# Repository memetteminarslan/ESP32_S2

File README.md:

# ESP32C3_Kicanvas
readme memin

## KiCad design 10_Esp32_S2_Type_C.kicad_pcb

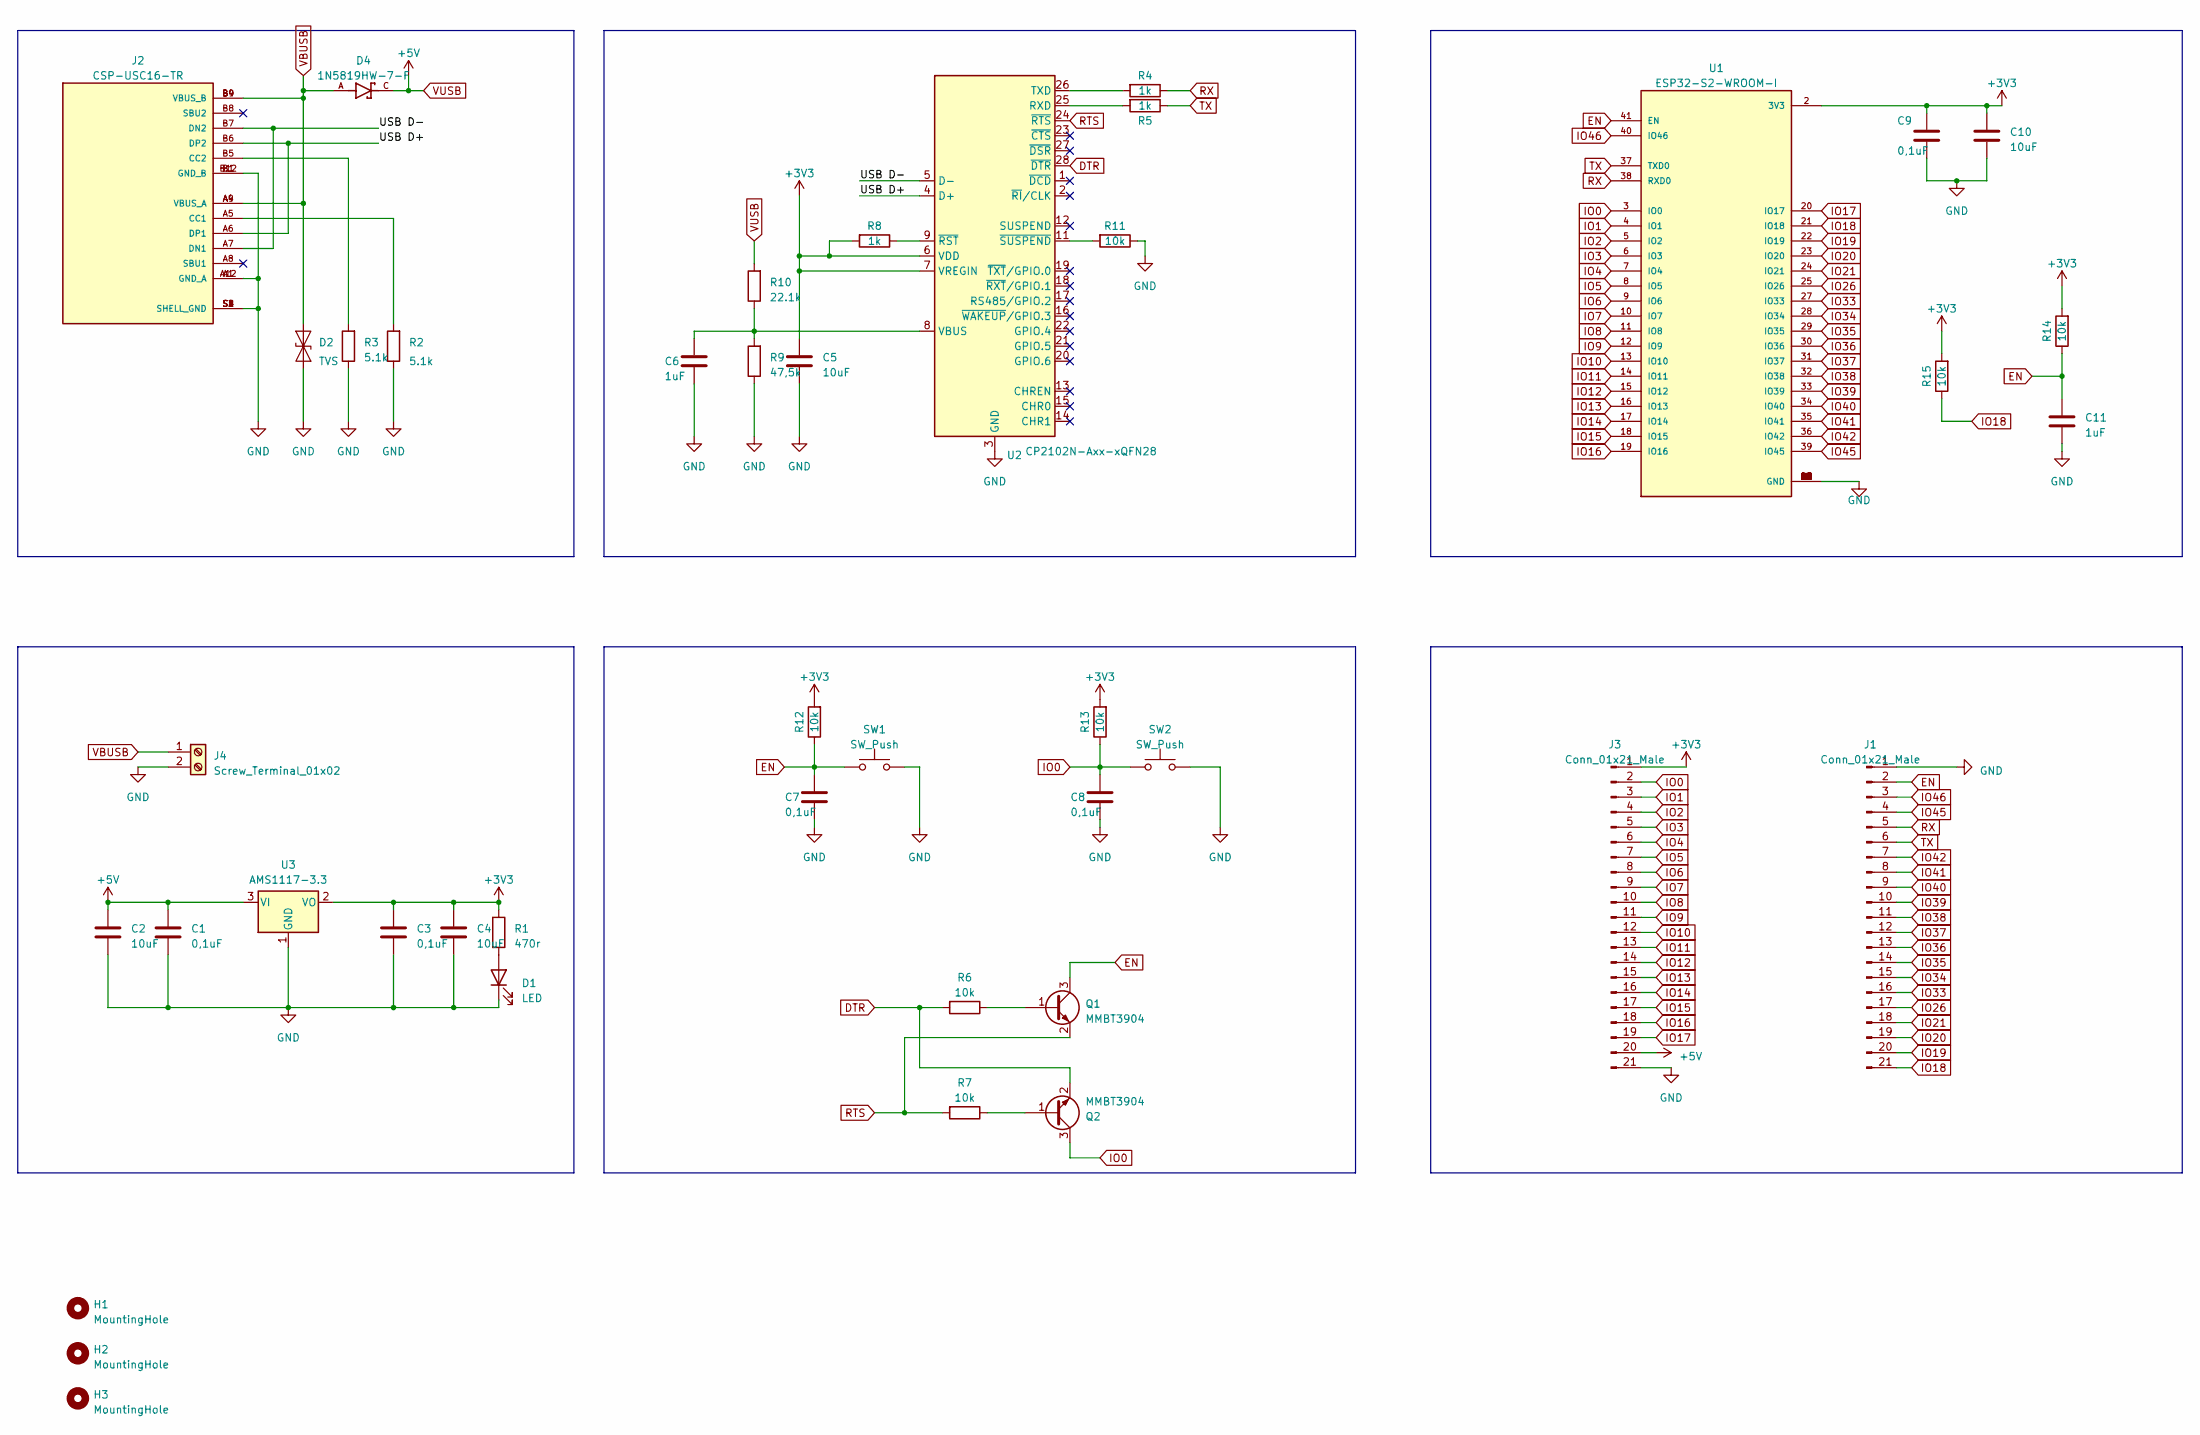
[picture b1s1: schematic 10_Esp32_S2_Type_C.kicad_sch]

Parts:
C1, C3, C7, C8, C9: 0,1uF; C_0603_1608Metric
C2, C4, C5, C10: 10uF; C_0603_1608Metric
C6, C11: 1uF; C_0603_1608Metric
D1: LED; LED_0603_1608Metric
D2: TVS; D_SOD-323
D4: 1N5819HW-7-F; SOD3715X145N; PARTREV 18-2
H1, H2, H3: MountingHole; MountingHole_2.5mm
J1, J3: Conn_01x21_Male; PinHeader_1x21_P2.54mm_Vertical
J2: CSP-USC16-TR; VALCON_CSP-USC16-TR; PARTREV A0
J4: Screw_Terminal_01x02; PinHeader_1x02_P2.54mm_Vertical
Q1, Q2: MMBT3904; SOT-23
R1: 470r; R_0603_1608Metric
R2, R3: 5.1k; R_0402_1005Metric
R4, R5, R8: 1k; R_0603_1608Metric
R6, R7, R11, R12, R13, R14, R15: 10k; R_0603_1608Metric
R9: 47,5k; R_0603_1608Metric
R10: 22.1k; R_0603_1608Metric
SW1, SW2: SW_Push; SW_TL1015AF160QG
U1: ESP32-S2-WROOM-I; ESP32-S2-WROOM; PARTREV v1.3
U2: CP2102N-Axx-xQFN28; QFN-28-1EP_5x5mm_P0.5mm_EP3.35x3.35mm
U3: AMS1117-3.3; SOT-223-3_TabPin2

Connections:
+3V3: C3.1, C4.1, C5.1, C9.1, C10.1, J3.1, R1.1, R8.2, R12.2, R13.2, R14.2, R15.2, U1.2 (3V3), U2.6 (VDD), U2.7 (VREGIN), U3.2 (VO)
/USB D+: J2.A6 (DP1), J2.B6 (DP2), U2.4 (D+)
/USB D-: J2.A7 (DN1), J2.B7 (DN2), U2.5 (D-)
DTR: Q2.2 (E), R6.2, U2.28 (~DTR)
EN: C7.1, C11.1, J1.2, Q1.3 (C), R12.1, R14.1, SW1.1, U1.41 (EN); also elsewhere on the board
GND: C1.2, C2.2, C3.2, C4.2, C5.2, C6.2, C7.2, C8.2, C9.2, C10.2, C11.2, D1.1 (K), D2.1 (A1), J1.1, J2.A1 (GND_A), J2.A12 (GND_A), J2.B1 (GND_B), J2.B12 (GND_B), J2.S1 (SHELL_GND), J2.S2 (SHELL_GND), J2.S3 (SHELL_GND), J2.S4 (SHELL_GND), J3.21, J4.2, R2.1, R3.1, R9.1, R11.1, SW1.2, SW2.2, U1.1 (GND), U1.26 (GND), U1.42 (GND), U1.43 (GND), U1.44 (GND), U1.45 (GND), U1.46 (GND), U1.47 (GND), U1.48 (GND), U1.49 (GND), U1.50 (GND), U1.51 (GND), U2.3 (GND), U2.29 (GND), U3.1 (GND); also elsewhere on the board
IO0: C8.1, J3.2, Q2.3 (C), R13.1, SW2.1, U1.3 (IO0); also elsewhere on the board
IO1: J3.3, U1.4 (IO1)
IO2: J3.4, U1.5 (IO2)
IO3: J3.5, U1.6 (IO3)
IO4: J3.6, U1.7 (IO4)
IO5: J3.7, U1.8 (IO5)
IO6: J3.8, U1.9 (IO6)
IO7: J3.9, U1.10 (IO7)
IO8: J3.10, U1.11 (IO8)
IO9: J3.11, U1.12 (IO9)
IO10: J3.12, U1.13 (IO10)
IO11: J3.13, U1.14 (IO11)
IO12: J3.14, U1.15 (IO12)
IO13: J3.15, U1.16 (IO13)
IO14: J3.16, U1.17 (IO14)
IO15: J3.17, U1.18 (IO15)
IO16: J3.18, U1.19 (IO16)
IO17: J3.19, U1.20 (IO17)
IO18: J1.21, R15.1, U1.21 (IO18)
IO19: J1.20, U1.22 (IO19)
IO20: J1.19, U1.23 (IO20)
IO21: J1.18, U1.24 (IO21)
IO26: J1.17, U1.25 (IO26)
IO33: J1.16, U1.27 (IO33)
IO34: J1.15, U1.28 (IO34)
IO35: J1.14, U1.29 (IO35)
IO36: J1.13, U1.30 (IO36)
IO37: J1.12, U1.31 (IO37)
IO38: J1.11, U1.32 (IO38)
IO39: J1.10, U1.33 (IO39)
IO40: J1.9, U1.34 (IO40)
IO41: J1.8, U1.35 (IO41)
IO42: J1.7, U1.36 (IO42)
IO45: J1.4, U1.39 (IO45)
IO46: J1.3, U1.40 (IO46)
unnamed: D1.2 (A), R1.2
unnamed: J2.A5 (CC1), R2.2
unnamed: J2.B5 (CC2), R3.2
unnamed: Q1.1 (B), R6.1
unnamed: Q2.1 (B), R7.1
unnamed: R5.2, U2.25 (RXD)
unnamed: R4.2, U2.26 (TXD)
unnamed: C6.1, R9.2, R10.1, U2.8 (VBUS)
unnamed: R8.1, U2.9 (~RST)
unnamed: R11.2, U2.11 (~SUSPEND)
RTS: Q1.2 (E), R7.2, U2.24 (~RTS)
RX: J1.5, R4.1, U1.38 (RXD0)
TX: J1.6, R5.1, U1.37 (TXD0)
VBUSB: D2.2 (A2), D4.A, J2.A4 (VBUS_A), J2.A9 (VBUS_A), J2.B4 (VBUS_B), J2.B9 (VBUS_B), J4.1
VUSB: C1.1, C2.1, D4.C, J3.20, R10.2, U3.3 (VI)

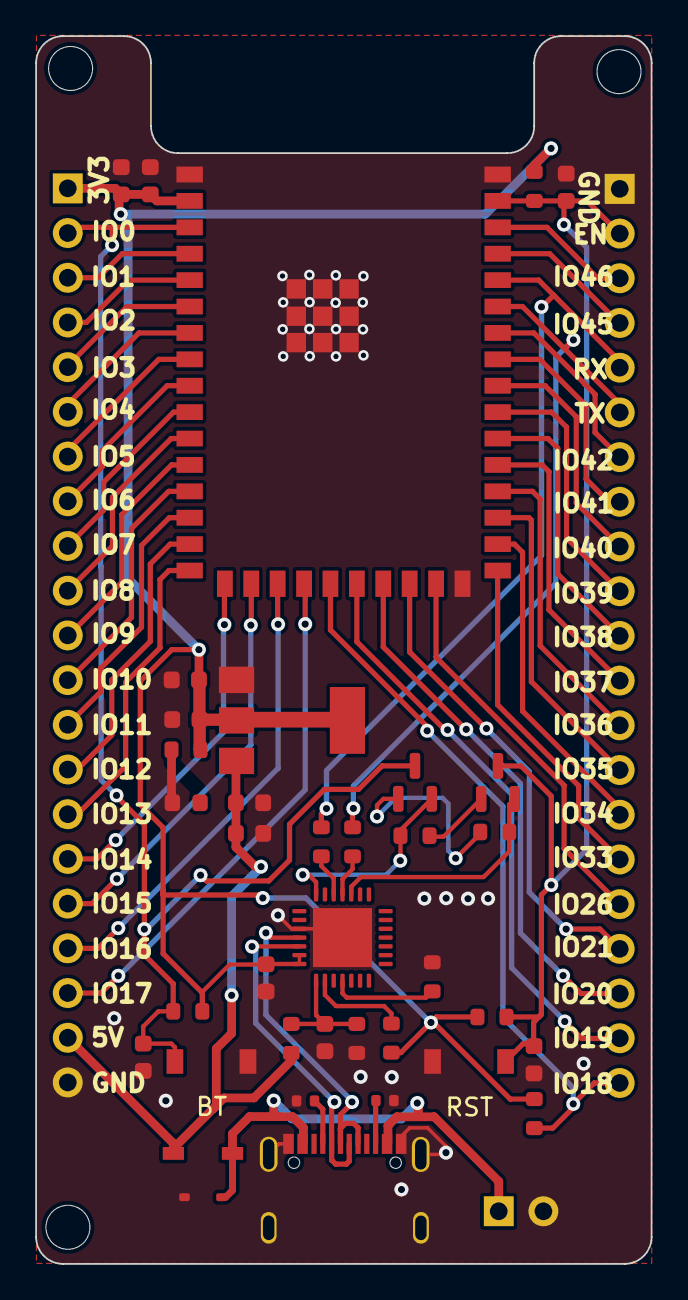
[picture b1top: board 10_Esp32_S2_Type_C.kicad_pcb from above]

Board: 2 copper layers, 35.0 x 69.8 mm, 43 parts (0 on the bottom side), 56 nets.

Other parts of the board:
BT: SW_Push; SW_TL1015AF160QG
RST: SW_Push; SW_TL1015AF160QG

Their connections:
EN: RST.1; also elsewhere on the board
GND: BT.2, RST.2; also elsewhere on the board
IO0: BT.1; also elsewhere on the board

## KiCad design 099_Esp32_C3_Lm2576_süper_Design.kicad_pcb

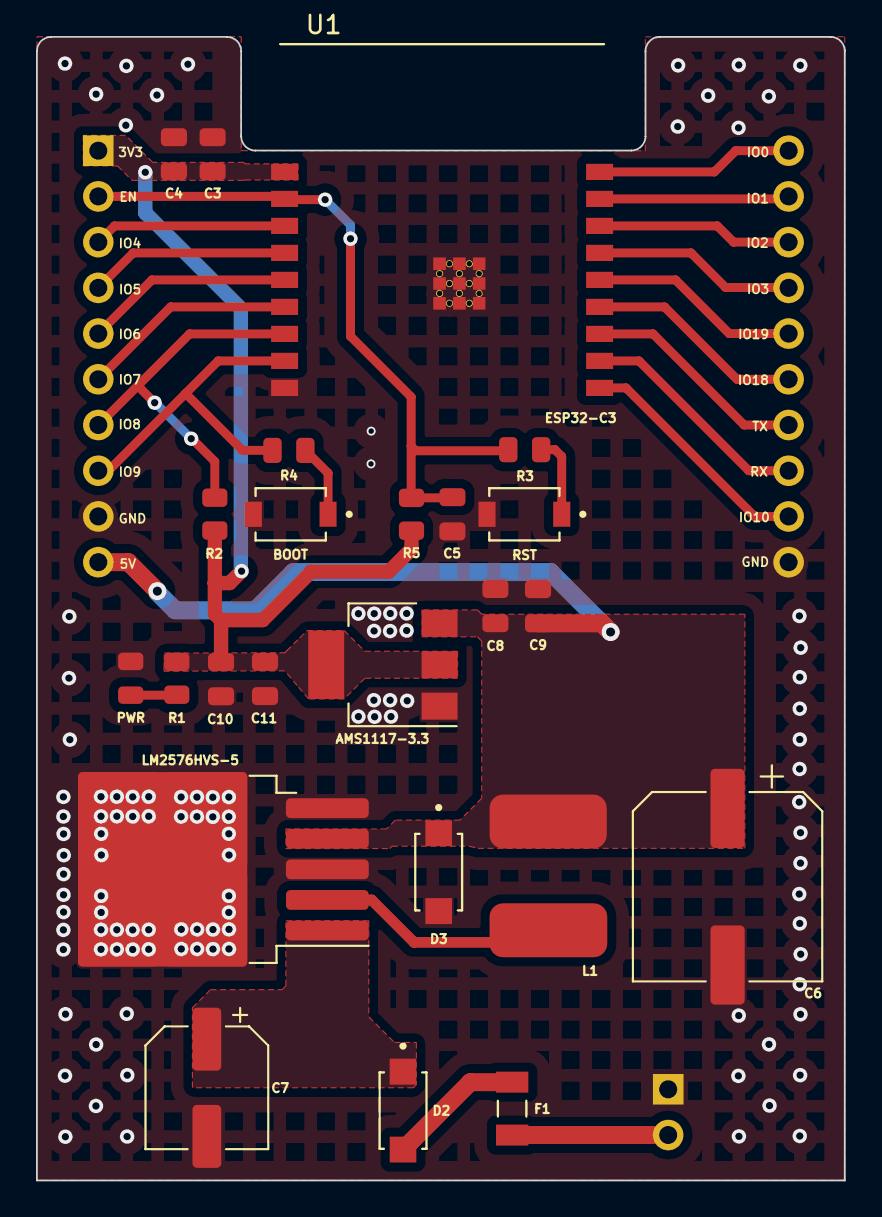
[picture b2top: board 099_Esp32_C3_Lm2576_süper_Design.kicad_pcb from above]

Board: 2 copper layers, 44.9 x 63.5 mm, 27 parts (0 on the bottom side), 26 nets.

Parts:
BOOT: SW_Push; SW_TL1015AF160QG
C3, C4, C5, C8, C9, C10, C11: C; C_0805_2012Metric
C6: C_Polarized_Small; CP_Elec_10x12.6
C7: C_Polarized_Small; CP_Elec_6.3x7.7
D2, D3: SS310ALH; SODFL5226X100N
F1: Fuse; FUSC3215X83N
J3: Screw_Terminal_01x02; PinHeader_1x02_P2.54mm_Vertical
J4, J5: Conn_01x10_Male; PinHeader_1x10_P2.54mm_Vertical
L1: L; 100uH
PWR: LED; LED_0805_2012Metric
R1, R2, R3, R4, R5: R; R_0805_2012Metric
RST: SW_Push; SW_TL1015AF160QG
U1: ESP32-C3; MODULE_ESP32-C3-WROOM-02-H4
U2: LM2576HVS-5; TO-263-5_TabPin3
U3: AMS1117-3.3; SOT-223-3_TabPin2

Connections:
+3V3: C3.1, C4.1, C10.1, C11.1, J4.1, R1.1, R2.1, R5.1, U1.1 (3V3), U3.2 (VO)
+5V: C6.1, C8.1, C9.1, D3.1, J4.10, L1.2, U2.4 (FB), U3.3 (VI)
+12V: F1.1, J3.2
EN: C5.1, J4.2, R3.1, R5.2, U1.2 (EN)
GND: BOOT.2, C3.2, C4.2, C5.2, C6.2, C7.2, C8.2, C9.2, C10.2, C11.2, D3.2, J3.1, J4.9, J5.10, PWR.1 (K), RST.2, U1.9 (GND), U1.19 (GND), U1.20 (GND), U1.21 (GND), U1.22 (GND), U1.23 (GND), U1.24 (GND), U1.25 (GND), U1.26 (GND), U1.27 (GND), U1.28 (GND), U1.29 (GND), U1.30 (GND), U1.31 (GND), U1.32 (GND), U1.33 (GND), U1.34 (GND), U1.35 (GND), U1.36 (GND), U1.37 (GND), U1.38 (GND), U2.3 (GND), U2.5 (~ON/OFF), U3.1 (GND)
IO0: J5.1, U1.18 (IO0)
IO1: J5.2, U1.17 (IO1)
IO2: J5.3, U1.16 (IO2)
IO3: J5.4, U1.15 (IO3)
IO4: J4.3, U1.3 (IO4)
IO5: J4.4, U1.4 (IO5)
IO6: J4.5, U1.5 (IO6)
IO7: J4.6, U1.6 (IO7)
IO8: J4.7, R2.2, U1.7 (IO8)
IO9: J4.8, R4.1, U1.8 (IO9)
IO10: J5.9, U1.10 (IO10)
IO18: J5.6, U1.13 (IO18)
IO19: J5.5, U1.14 (IO19)
unnamed: PWR.2 (A), R1.2
unnamed: D2.2, F1.2
unnamed: R3.2, RST.1
unnamed: BOOT.1, R4.2
unnamed: L1.1, U2.2 (OUT)
unnamed: C7.1, D2.1, U2.1 (VIN)
RX: J5.8, U1.11 (RXD)
TX: J5.7, U1.12 (TXD)

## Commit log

2023-05-04 Create c3_shematic
